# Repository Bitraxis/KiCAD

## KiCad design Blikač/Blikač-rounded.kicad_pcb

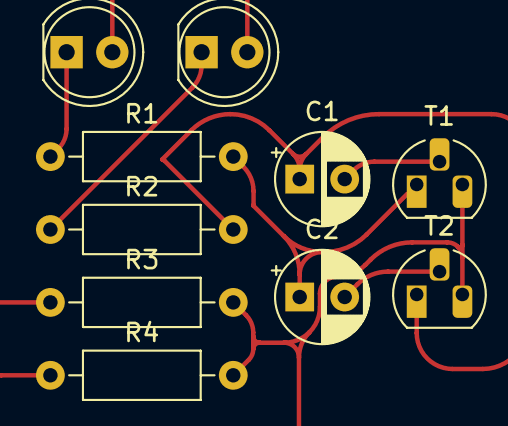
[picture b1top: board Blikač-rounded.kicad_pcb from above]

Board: 2 copper layers, 10 parts (0 on the bottom side), 8 nets.

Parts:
C1, C2: 10µF; CP_Radial_D5.0mm_P2.50mm
D1, D2: LED; LED_D5.0mm
R1, R2: 1K2; R_Axial_DIN0207_L6.3mm_D2.5mm_P10.16mm_Horizontal
R3, R4: 47K; R_Axial_DIN0207_L6.3mm_D2.5mm_P10.16mm_Horizontal
T1, T2: BC547; TO-92L_HandSolder

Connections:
+9V: D1.2 (A), D2.2 (A), R3.1, R4.1
GND: R3.2, R4.2, T1.3 (E), T2.3 (E)
unnamed: D1.1 (K), R1.1
unnamed: D2.1 (K), R2.1
unnamed: C1.2, T1.2 (B)
unnamed: C2.1, R1.2, T1.1 (C)
unnamed: C2.2, T2.2 (B)
unnamed: C1.1, R2.2, T2.1 (C)
